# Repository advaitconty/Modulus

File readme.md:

# Modulus

A keyboard, built with the idea of expansion in the future, through SPI.

Things I will do later in the future (with other Hack Club events, or with my own money):
- Numpad over SPI
- Macropad over SPI

Just use it like a keyboard! However, any SPI accessories should be connected while the keyboard is powered down. This is mainly a limitation of SPI, as it is not hot-plug compatible.
The USB ports are USB 2.0 only, so it's better to be used for stuff like USB sound cards and mice.
I don't actually know how much lag will the ports create, because they're bottom mounted, in direct contact with foam, and is air cooled. So it may overheat (tried to add thermal dissiptation vias but effectiveness not tested)

Quirks:
- Case has holes at the bottom for cooling (yes I'm serious)

## Images

- model + board

- board only

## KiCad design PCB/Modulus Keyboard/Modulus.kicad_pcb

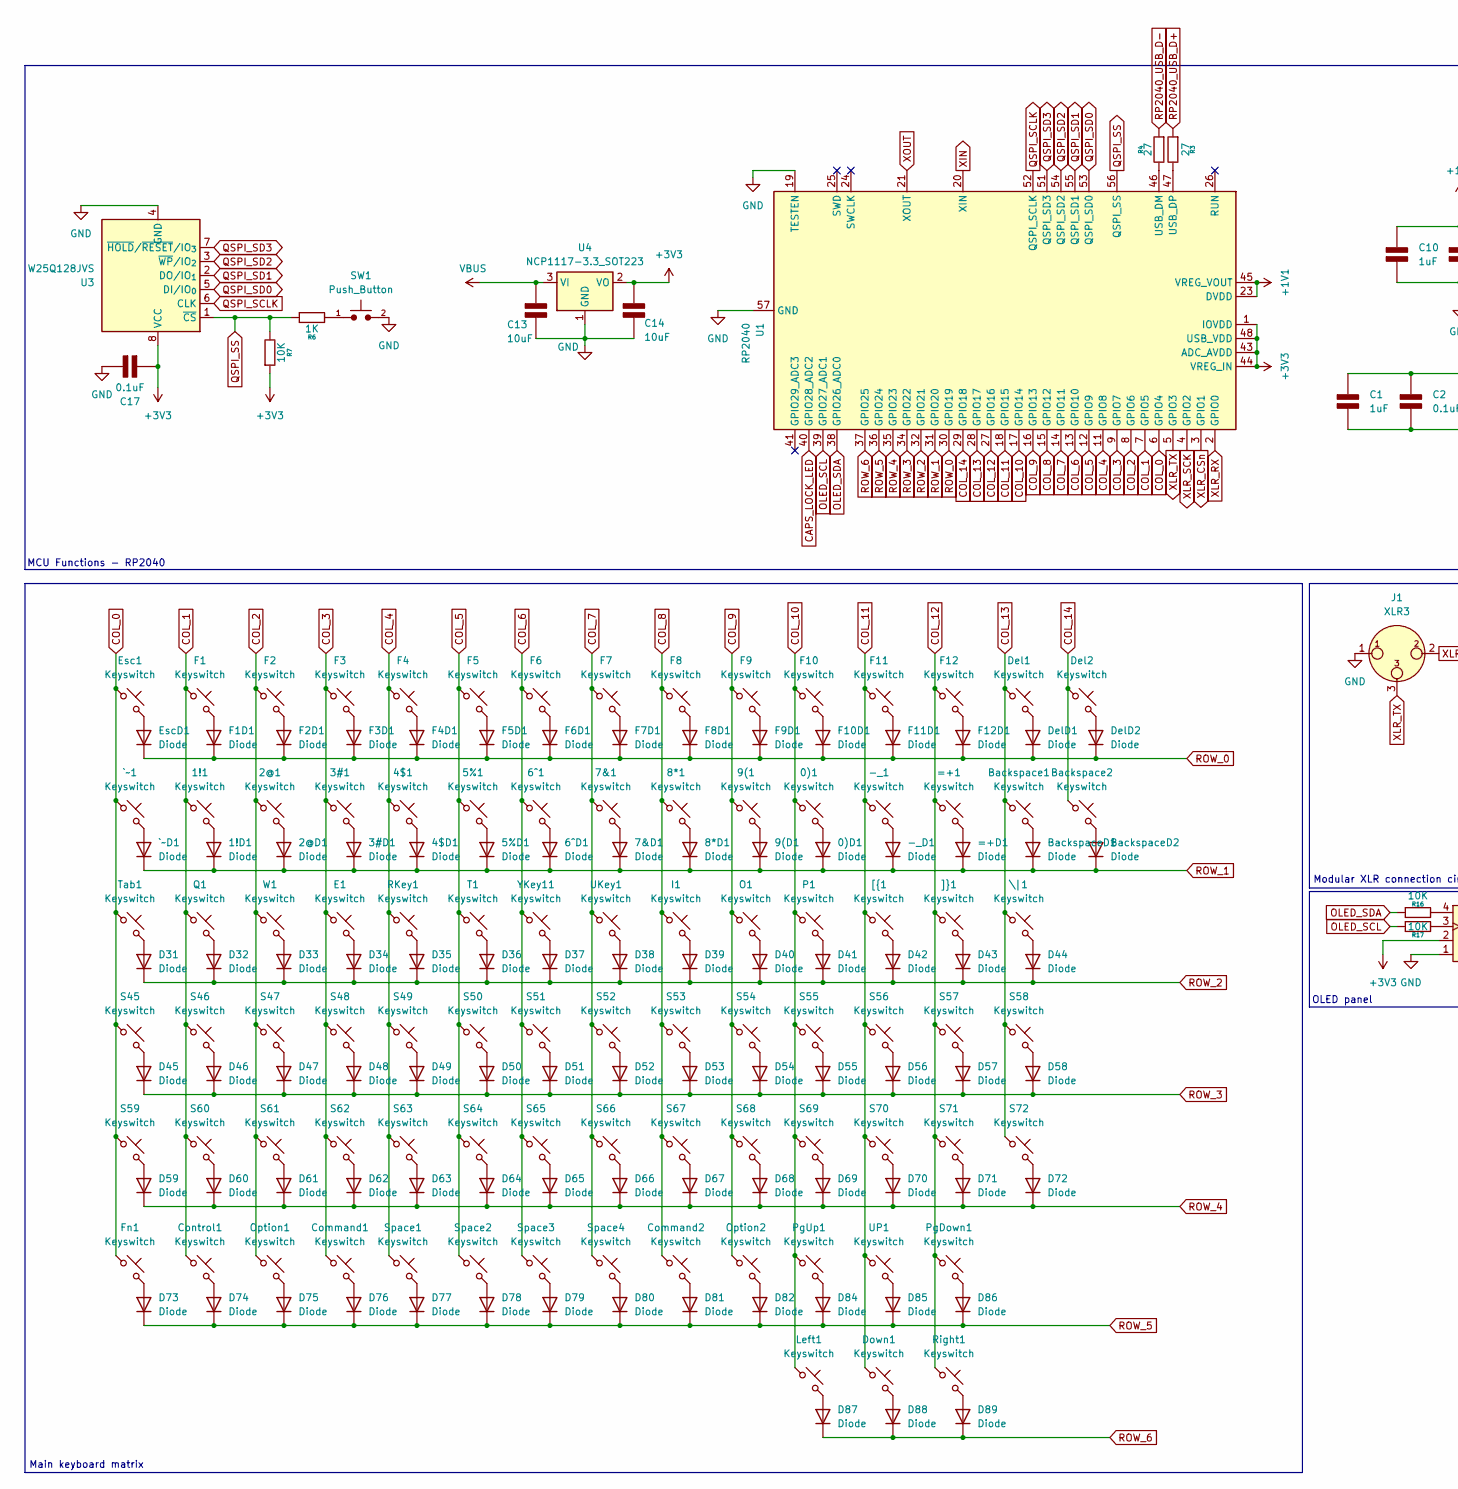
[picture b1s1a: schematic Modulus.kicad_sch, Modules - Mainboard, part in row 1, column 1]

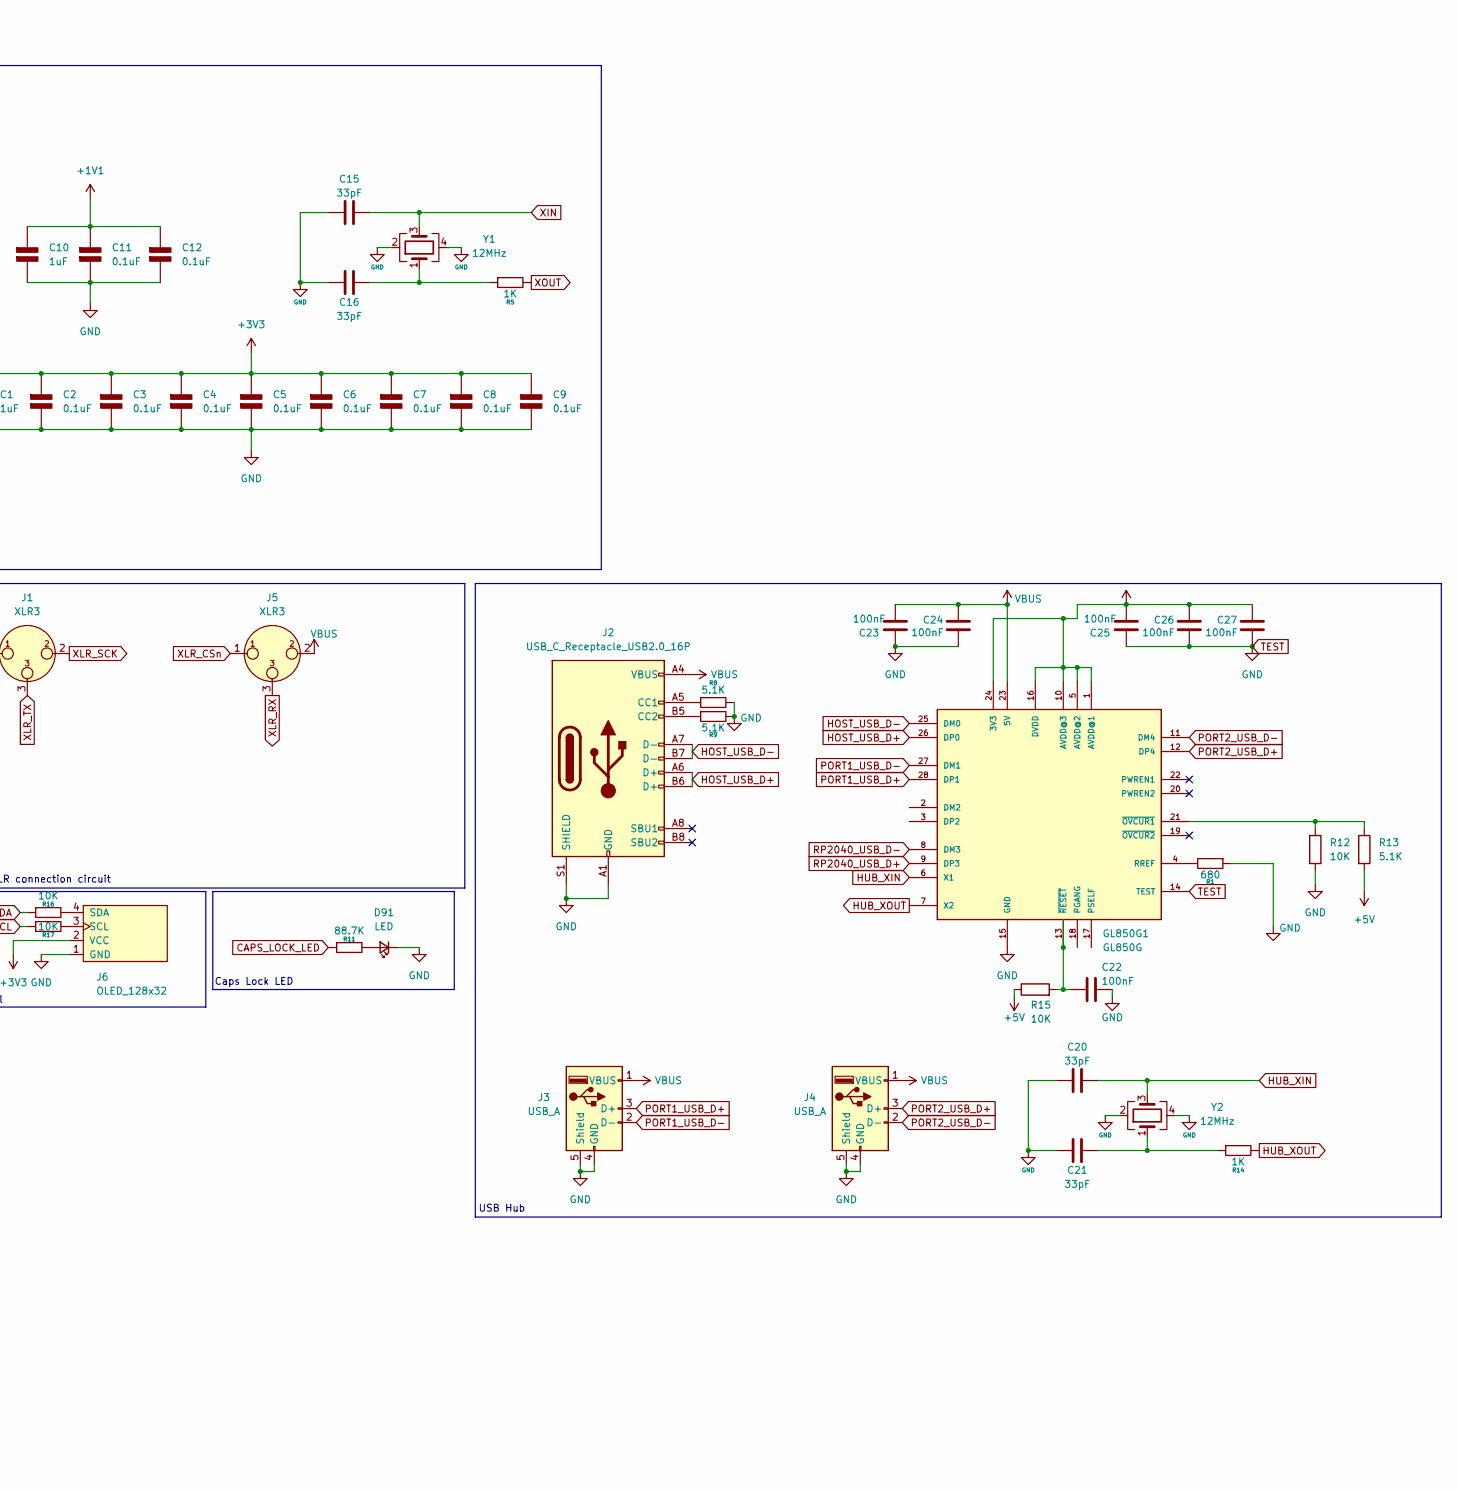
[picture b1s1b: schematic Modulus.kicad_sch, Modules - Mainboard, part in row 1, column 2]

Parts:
0)1, 1!1, 2@1, 3#1, 4$1, 5%1, 6^1, 7&1, 8*1, 9(1: Keyswitch; SW_Hotswap_Kailh_MX_1.00u; JLCPCB Part # C41430893
0)D1, 1!D1, 2@D1, 3#D1, 4$D1, 5%D1, 6^D1, 7&D1, 8*D1, 9(D1: Diode; D_SMA; JLCPCB Part # C81598
-_1: Keyswitch; SW_Hotswap_Kailh_MX_1.00u; JLCPCB Part # C41430893
-_D1: Diode; D_SMA; JLCPCB Part # C81598
=+1: Keyswitch; SW_Hotswap_Kailh_MX_1.00u; JLCPCB Part # C41430893
=+D1: Diode; D_SMA; JLCPCB Part # C81598
Backspace1, Backspace2: Keyswitch; SW_Hotswap_Kailh_MX_1.00u; JLCPCB Part # C41430893
BackspaceD1, BackspaceD2: Diode; D_SMA; JLCPCB Part # C81598
C1, C10: 1uF; C_1206_3216Metric; Rating V; JLCPCB Part # C1848
C2, C3, C4, C5, C6, C7, C8, C9, C11, C12, C17: 0.1uF; C_1206_3216Metric; Rating V; JLCPCB Part # C24497
C13, C14: 10uF; C_1206_3216Metric; Rating V; JLCPCB Part # C13585
C15, C16, C20, C21: 33pF; C_0805_2012Metric; JLCPCB Part # C107115
C22, C23, C24, C25, C26, C27: 100nF; C_1206_3216Metric; JLCPCB Part # C1848
Command1, Command2: Keyswitch; SW_Hotswap_Kailh_MX_1.00u; JLCPCB Part # C41430893
Control1: Keyswitch; SW_Hotswap_Kailh_MX_1.00u; JLCPCB Part # C41430893
D31, D32, D33, D34, D35, D36, D37, D38, D39, D40, D41, D42, D43, D44, D45, D46, D47, D48, D49, D50, D51, D52, D53, D54, D55, D56, D57, D58, D59, D60, D61, D62, D63, D64, D65, D66, D67, D68, D69, D70, D71, D72, D73, D74, D75, D76, D77, D78, D79, D80, D81, D82, D84, D85, D86, D87, D88, D89: Diode; D_SMA; JLCPCB Part # C81598
D91: LED; LED_D5.0mm
Del1, Del2: Keyswitch; SW_Hotswap_Kailh_MX_1.00u; JLCPCB Part # C41430893
DelD1, DelD2: Diode; D_SMA; JLCPCB Part # C81598
Down1: Keyswitch; SW_Hotswap_Kailh_MX_1.00u; JLCPCB Part # C41430893
E1: Keyswitch; SW_Hotswap_Kailh_MX_1.00u; JLCPCB Part # C41430893
Esc1: Keyswitch; SW_Hotswap_Kailh_MX_1.00u; JLCPCB Part # C41430893
EscD1: Diode; D_SMA; JLCPCB Part # C81598
F1, F2, F3, F4, F5, F6, F7, F8, F9, F10, F11, F12: Keyswitch; SW_Hotswap_Kailh_MX_1.00u; JLCPCB Part # C41430893
F1D1, F2D1, F3D1, F4D1, F5D1, F6D1, F7D1, F8D1, F9D1, F10D1, F11D1, F12D1: Diode; D_SMA; JLCPCB Part # C81598
Fn1: Keyswitch; SW_Hotswap_Kailh_MX_1.00u; JLCPCB Part # C41430893
GL850G1: GL850G; 28SSOP; JLCPCB Part # C7501406
I1: Keyswitch; SW_Hotswap_Kailh_MX_1.00u; JLCPCB Part # C41430893
J1, J5: XLR3; NEUTRIK_NC3FAAH; JLCPCB Part # C368521
J2: USB_C_Receptacle_USB2.0_16P; USB_C_HRO_TYPE-C-31-M-12; JLCPCB Part # C165948
J3, J4: USB_A; GCT_USB1046-GF-0190-L-B-A_REVB4; JLCPCB Part # C6307429
J6: OLED_128x32
Left1: Keyswitch; SW_Hotswap_Kailh_MX_1.00u; JLCPCB Part # C41430893
O1: Keyswitch; SW_Hotswap_Kailh_MX_1.00u; JLCPCB Part # C41430893
Option1, Option2: Keyswitch; SW_Hotswap_Kailh_MX_1.00u; JLCPCB Part # C41430893
P1: Keyswitch; SW_Hotswap_Kailh_MX_1.00u; JLCPCB Part # C41430893
PgDown1: Keyswitch; SW_Hotswap_Kailh_MX_1.00u; JLCPCB Part # C41430893
PgUp1: Keyswitch; SW_Hotswap_Kailh_MX_1.00u; JLCPCB Part # C41430893
Q1: Keyswitch; SW_Hotswap_Kailh_MX_1.00u; JLCPCB Part # C41430893
R1: 680; R_0805_2012Metric; JLCPCB Part # C17798
R3, R4: 27; R_0805_2012Metric; JLCPCB Part # C17594
R5, R6, R14: 1K; R_1206_3216Metric; JLCPCB Part # C4410
R7, R12, R15, R16, R17: 10K; R_1206_3216Metric; JLCPCB Part # C17902
R8, R9, R13: 5.1K; R_0805_2012Metric; JLCPCB Part # C27834
R11: 88.7K; R_0402_1005Metric; JLCPCB Part # C25922
RKey1: Keyswitch; SW_Hotswap_Kailh_MX_1.00u; JLCPCB Part # C41430893
Right1: Keyswitch; SW_Hotswap_Kailh_MX_1.00u; JLCPCB Part # C41430893
S45: Keyswitch; SW_Hotswap_Kailh_MX_1.75u; JLCPCB Part # C41430893
S46, S47, S48, S49, S50, S51, S52, S53, S54, S55, S56, S57, S61, S62, S63, S64, S65, S66, S67, S68, S69, S70, S71: Keyswitch; SW_Hotswap_Kailh_MX_1.00u; JLCPCB Part # C41430893
S58, S59, S60: Keyswitch; SW_Hotswap_Kailh_MX_1.25u; JLCPCB Part # C41430893
S72: Keyswitch; SW_Hotswap_Kailh_MX_1.50u; JLCPCB Part # C41430893
SW1: Push_Button; SW_PUSH_6mm
Space1, Space2, Space3, Space4: Keyswitch; SW_Hotswap_Kailh_MX_1.50u; JLCPCB Part # C41430893
T1: Keyswitch; SW_Hotswap_Kailh_MX_1.00u; JLCPCB Part # C41430893
Tab1: Keyswitch; SW_Hotswap_Kailh_MX_1.50u; JLCPCB Part # C41430893
U1: RP2040; QFN-56-1EP_7x7mm_P0.4mm_EP3.2x3.2mm; JLCPCB Part # C2040
U3: W25Q128JVS; SOIC-8_5.3x5.3mm_P1.27mm; JLCPCB Part # C97521
U4: NCP1117-3.3_SOT223; SOT-223-3_TabPin2; JLCPCB Part # C26537
UKey1: Keyswitch; SW_Hotswap_Kailh_MX_1.00u; JLCPCB Part # C41430893
UP1: Keyswitch; SW_Hotswap_Kailh_MX_1.00u; JLCPCB Part # C41430893
W1: Keyswitch; SW_Hotswap_Kailh_MX_1.00u; JLCPCB Part # C41430893
Y1, Y2: 12MHz; Crystal_SMD_3225-4Pin_3.2x2.5mm; JLCPCB Part # C9002
YKey11: Keyswitch; SW_Hotswap_Kailh_MX_1.00u; JLCPCB Part # C41430893
[{1: Keyswitch; SW_Hotswap_Kailh_MX_1.00u; JLCPCB Part # C41430893
\|1: Keyswitch; SW_Hotswap_Kailh_MX_1.50u; JLCPCB Part # C41430893
]}1: Keyswitch; SW_Hotswap_Kailh_MX_1.00u; JLCPCB Part # C41430893
`~1: Keyswitch; SW_Hotswap_Kailh_MX_1.00u; JLCPCB Part # C41430893
`~D1: Diode; D_SMA; JLCPCB Part # C81598

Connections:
+1V1: C10.1 (+), C11.1 (+), C12.1 (+), U1.23 (DVDD), U1.45 (VREG_VOUT), U1.50 (DVDD)
+3V3: C1.1 (+), C2.1 (+), C3.1 (+), C4.1 (+), C5.1 (+), C6.1 (+), C7.1 (+), C8.1 (+), C9.1 (+), C14.1 (+), C17.1 (+), C25.2, C26.2, C27.2, GL850G1.1 (AVDD@1), GL850G1.5 (AVDD@2), GL850G1.10 (AVDD@3), GL850G1.16 (DVDD), GL850G1.24 (3V3), J6.2 (VCC), R7.1, U1.1 (IOVDD), U1.10 (IOVDD), U1.22 (IOVDD), U1.33 (IOVDD), U1.42 (IOVDD), U1.43 (ADC_AVDD), U1.44 (VREG_IN), U1.48 (USB_VDD), U1.49 (IOVDD), U3.8 (VCC), U4.2 (VO)
+5V: R13.2, R15.1
CAPS_LOCK_LED: R11.1, U1.40 (GPIO28_ADC2)
COL_0: Esc1.1, Fn1.1, S45.1, S59.1, Tab1.1, U1.6 (GPIO4), `~1.1
COL_1: 1!1.1, Control1.1, F1.1, Q1.1, S46.1, S60.1, U1.7 (GPIO5)
COL_2: 2@1.1, F2.1, Option1.1, S47.1, S61.1, U1.8 (GPIO6), W1.1
COL_3: 3#1.1, Command1.1, E1.1, F3.1, S48.1, S62.1, U1.9 (GPIO7)
COL_4: 4$1.1, F4.1, RKey1.1, S49.1, S63.1, Space1.1, U1.11 (GPIO8)
COL_5: 5%1.1, F5.1, S50.1, S64.1, Space2.1, T1.1, U1.12 (GPIO9)
COL_6: 6^1.1, F6.1, S51.1, S65.1, Space3.1, U1.13 (GPIO10), YKey11.1
COL_7: 7&1.1, F7.1, S52.1, S66.1, Space4.1, U1.14 (GPIO11), UKey1.1
COL_8: 8*1.1, Command2.1, F8.1, I1.1, S53.1, S67.1, U1.15 (GPIO12)
COL_9: 9(1.1, F9.1, O1.1, Option2.1, S54.1, S68.1, U1.16 (GPIO13)
COL_10: 0)1.1, F10.1, Left1.1, P1.1, PgUp1.1, S55.1, S69.1, U1.17 (GPIO14)
COL_11: -_1.1, Down1.1, F11.1, S56.1, S70.1, U1.18 (GPIO15), UP1.1, [{1.1
COL_12: =+1.1, F12.1, PgDown1.1, Right1.1, S57.1, S71.1, U1.27 (GPIO16), ]}1.1
COL_13: Backspace1.1, Del1.1, S58.1, S72.1, U1.28 (GPIO17), \|1.1
COL_14: Backspace2.1, Del2.1, U1.29 (GPIO18)
HOST_USB_D+: GL850G1.26 (DP0), J2.A6 (D+), J2.B6 (D+)
HOST_USB_D-: GL850G1.25 (DM0), J2.A7 (D-), J2.B7 (D-)
HUB_XIN: C20.2, GL850G1.6 (X1), Y2.3
HUB_XOUT: GL850G1.7 (X2), R14.2
unnamed: 0)1.2, 0)D1.2 (A)
unnamed: 1!1.2, 1!D1.2 (A)
unnamed: 2@1.2, 2@D1.2 (A)
unnamed: 3#1.2, 3#D1.2 (A)
unnamed: 4$1.2, 4$D1.2 (A)
unnamed: 5%1.2, 5%D1.2 (A)
unnamed: 6^1.2, 6^D1.2 (A)
unnamed: 7&1.2, 7&D1.2 (A)
unnamed: 8*1.2, 8*D1.2 (A)
unnamed: 9(1.2, 9(D1.2 (A)
unnamed: -_1.2, -_D1.2 (A)
unnamed: =+1.2, =+D1.2 (A)
unnamed: Backspace1.2, BackspaceD1.2 (A)
unnamed: Backspace2.2, BackspaceD2.2 (A)
unnamed: C16.2, R5.1, Y1.1
unnamed: C21.2, R14.1, Y2.1
unnamed: D31.2 (A), Tab1.2
unnamed: D32.2 (A), Q1.2
unnamed: D33.2 (A), W1.2
unnamed: D34.2 (A), E1.2
unnamed: D35.2 (A), RKey1.2
unnamed: D36.2 (A), T1.2
unnamed: D37.2 (A), YKey11.2
unnamed: D38.2 (A), UKey1.2
unnamed: D39.2 (A), I1.2
unnamed: D40.2 (A), O1.2
unnamed: D41.2 (A), P1.2
unnamed: D42.2 (A), [{1.2
unnamed: D43.2 (A), ]}1.2
unnamed: D44.2 (A), \|1.2
unnamed: D45.2 (A), S45.2
unnamed: D46.2 (A), S46.2
unnamed: D47.2 (A), S47.2
unnamed: D48.2 (A), S48.2
unnamed: D49.2 (A), S49.2
unnamed: D50.2 (A), S50.2
unnamed: D51.2 (A), S51.2
unnamed: D52.2 (A), S52.2
unnamed: D53.2 (A), S53.2
unnamed: D54.2 (A), S54.2
unnamed: D55.2 (A), S55.2
unnamed: D56.2 (A), S56.2
unnamed: D57.2 (A), S57.2
unnamed: D58.2 (A), S58.2
unnamed: D59.2 (A), S59.2
unnamed: D60.2 (A), S60.2
unnamed: D61.2 (A), S61.2
unnamed: D62.2 (A), S62.2
unnamed: D63.2 (A), S63.2
unnamed: D64.2 (A), S64.2
unnamed: D65.2 (A), S65.2
unnamed: D66.2 (A), S66.2
unnamed: D67.2 (A), S67.2
unnamed: D68.2 (A), S68.2
unnamed: D69.2 (A), S69.2
unnamed: D70.2 (A), S70.2
unnamed: D71.2 (A), S71.2
unnamed: D72.2 (A), S72.2
unnamed: D73.2 (A), Fn1.2
unnamed: Control1.2, D74.2 (A)
unnamed: D75.2 (A), Option1.2
unnamed: Command1.2, D76.2 (A)
unnamed: D77.2 (A), Space1.2
unnamed: D78.2 (A), Space2.2
unnamed: D79.2 (A), Space3.2
unnamed: D80.2 (A), Space4.2
unnamed: Command2.2, D81.2 (A)
unnamed: D82.2 (A), Option2.2
unnamed: D84.2 (A), PgUp1.2
unnamed: D85.2 (A), UP1.2
unnamed: D86.2 (A), PgDown1.2
unnamed: D87.2 (A), Left1.2
unnamed: D88.2 (A), Down1.2
unnamed: D89.2 (A), Right1.2
unnamed: D91.2 (A), R11.2
unnamed: Del1.2, DelD1.2 (A)
unnamed: Del2.2, DelD2.2 (A)
unnamed: Esc1.2, EscD1.2 (A)
unnamed: F1.2, F1D1.2 (A)
unnamed: F2.2, F2D1.2 (A)
unnamed: F3.2, F3D1.2 (A)
unnamed: F4.2, F4D1.2 (A)
unnamed: F5.2, F5D1.2 (A)
unnamed: F6.2, F6D1.2 (A)
unnamed: F7.2, F7D1.2 (A)
unnamed: F8.2, F8D1.2 (A)
unnamed: F9.2, F9D1.2 (A)
unnamed: F10.2, F10D1.2 (A)
unnamed: F11.2, F11D1.2 (A)
unnamed: F12.2, F12D1.2 (A)
unnamed: GL850G1.4 (RREF), R1.2
unnamed: GL850G1.21 (~OVCUR1), R12.1, R13.1
unnamed: C22.2, GL850G1.13 (~RESET), R15.2
unnamed: J2.A5 (CC1), R8.1
unnamed: J2.B5 (CC2), R9.1
unnamed: J6.3 (SCL), R17.2
unnamed: J6.4 (SDA), R16.2
unnamed: R6.2, SW1.1
unnamed: R4.2, U1.46 (USB_DM)
unnamed: R3.2, U1.47 (USB_DP)
unnamed: `~1.2, `~D1.2 (A)
OLED_SCL: R17.1, U1.39 (GPIO27_ADC1)
OLED_SDA: R16.1, U1.38 (GPIO26_ADC0)
PORT1_USB_D+: GL850G1.28 (DP1), J3.3 (D+)
PORT1_USB_D-: GL850G1.27 (DM1), J3.2 (D-)
PORT2_USB_D+: GL850G1.12 (DP4), J4.3 (D+)
PORT2_USB_D-: GL850G1.11 (DM4), J4.2 (D-)
QSPI_SCLK: U1.52 (QSPI_SCLK), U3.6 (CLK)
QSPI_SD0: U1.53 (QSPI_SD0), U3.5 (DI/IO_{0})
QSPI_SD1: U1.55 (QSPI_SD1), U3.2 (DO/IO_{1})
QSPI_SD2: U1.54 (QSPI_SD2), U3.3 (~WP/IO_{2})
QSPI_SD3: U1.51 (QSPI_SD3), U3.7 (~HOLD/~RESET/IO_{3})
QSPI_SS: R6.1, R7.2, U1.56 (QSPI_SS), U3.1 (~CS)
ROW_0: DelD1.1 (K), DelD2.1 (K), EscD1.1 (K), F1D1.1 (K), F2D1.1 (K), F3D1.1 (K), F4D1.1 (K), F5D1.1 (K), F6D1.1 (K), F7D1.1 (K), F8D1.1 (K), F9D1.1 (K), F10D1.1 (K), F11D1.1 (K), F12D1.1 (K), U1.30 (GPIO19)
ROW_1: 0)D1.1 (K), 1!D1.1 (K), 2@D1.1 (K), 3#D1.1 (K), 4$D1.1 (K), 5%D1.1 (K), 6^D1.1 (K), 7&D1.1 (K), 8*D1.1 (K), 9(D1.1 (K), -_D1.1 (K), =+D1.1 (K), BackspaceD1.1 (K), BackspaceD2.1 (K), U1.31 (GPIO20), `~D1.1 (K)
ROW_2: D31.1 (K), D32.1 (K), D33.1 (K), D34.1 (K), D35.1 (K), D36.1 (K), D37.1 (K), D38.1 (K), D39.1 (K), D40.1 (K), D41.1 (K), D42.1 (K), D43.1 (K), D44.1 (K), U1.32 (GPIO21)
ROW_3: D45.1 (K), D46.1 (K), D47.1 (K), D48.1 (K), D49.1 (K), D50.1 (K), D51.1 (K), D52.1 (K), D53.1 (K), D54.1 (K), D55.1 (K), D56.1 (K), D57.1 (K), D58.1 (K), U1.34 (GPIO22)
ROW_4: D59.1 (K), D60.1 (K), D61.1 (K), D62.1 (K), D63.1 (K), D64.1 (K), D65.1 (K), D66.1 (K), D67.1 (K), D68.1 (K), D69.1 (K), D70.1 (K), D71.1 (K), D72.1 (K), U1.35 (GPIO23)
ROW_5: D73.1 (K), D74.1 (K), D75.1 (K), D76.1 (K), D77.1 (K), D78.1 (K), D79.1 (K), D80.1 (K), D81.1 (K), D82.1 (K), D84.1 (K), D85.1 (K), D86.1 (K), U1.36 (GPIO24)
ROW_6: D87.1 (K), D88.1 (K), D89.1 (K), U1.37 (GPIO25)
RP2040_USB_D+: GL850G1.9 (DP3), R3.1
RP2040_USB_D-: GL850G1.8 (DM3), R4.1
TEST: C1.2 (-), C2.2 (-), C3.2 (-), C4.2 (-), C5.2 (-), C6.2 (-), C7.2 (-), C8.2 (-), C9.2 (-), C10.2 (-), C11.2 (-), C12.2 (-), C13.2 (-), C14.2 (-), C15.1, C16.1, C17.2 (-), C20.1, C21.1, C22.1, C23.1, C24.1, C25.1, C26.1, C27.1, D91.1 (K), GL850G1.14 (TEST), GL850G1.15 (GND), J1.1, J2.A1 (GND), J2.A12 (GND), J2.B1 (GND), J2.B12 (GND), J2.S1 (SHIELD), J3.4 (GND), J3.5 (Shield), J4.4 (GND), J4.5 (Shield), J6.1 (GND), R1.1, R8.2, R9.2, R12.2, SW1.2, U1.19 (TESTEN), U1.57 (GND), U3.4 (GND), U4.1 (GND), Y1.2, Y1.4, Y2.2, Y2.4
VBUS: C13.1 (+), C23.2, C24.2, GL850G1.23 (5V), J2.A4 (VBUS), J2.A9 (VBUS), J2.B4 (VBUS), J2.B9 (VBUS), J3.1 (VBUS), J4.1 (VBUS), J5.2, U4.3 (VI)
XIN: C15.2, U1.20 (XIN), Y1.3
XLR_CSn: J5.1, U1.3 (GPIO1)
XLR_RX: J5.3, U1.2 (GPIO0)
XLR_SCK: J1.2, U1.4 (GPIO2)
XLR_TX: J1.3, U1.5 (GPIO3)
XOUT: R5.2, U1.21 (XOUT)

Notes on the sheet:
Caps Lock LED
OLED panel
USB Hub
Modular XLR connection circuit
MCU Functions - RP2040
Main keyboard matrix

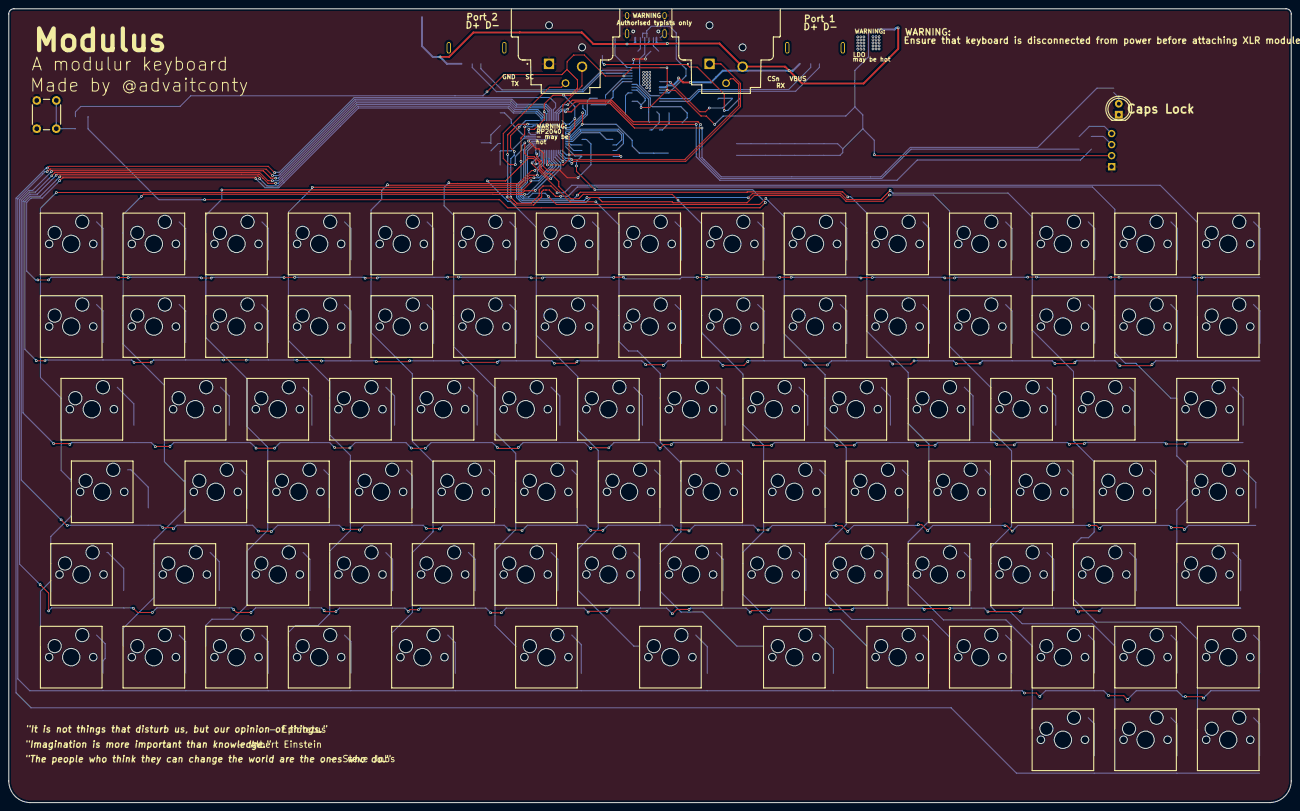
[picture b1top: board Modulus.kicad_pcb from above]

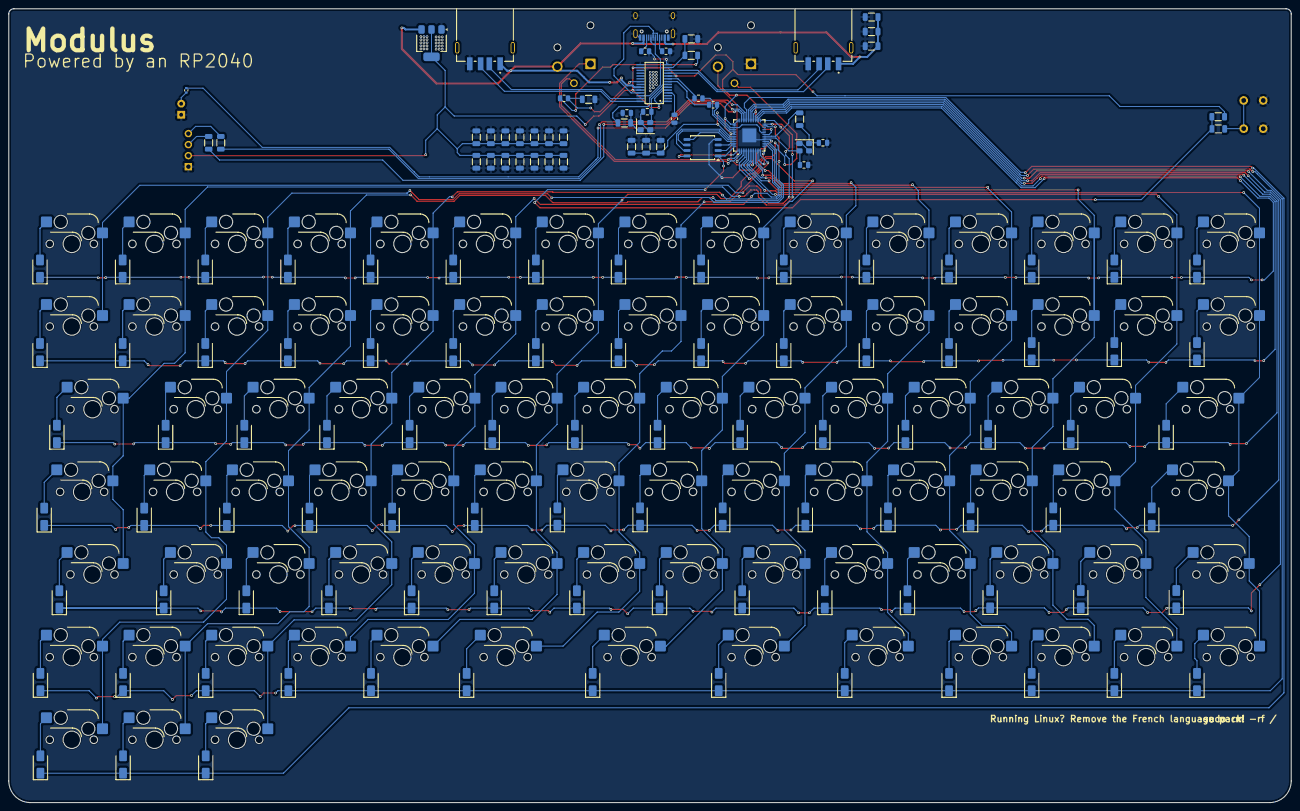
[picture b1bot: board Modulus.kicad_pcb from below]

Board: 2 copper layers, 295.6 x 183.0 mm, 230 parts (137 on the bottom side), 153 nets.

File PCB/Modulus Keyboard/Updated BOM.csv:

"Id";"Designator";"Footprint";"Quantity";"Designation";"Supplier and ref";
1;"U4";"SOT-223-3_TabPin2";1;"NCP1117-3.3_SOT223";;;
2;"Caps Lock";"0603";1;"LED";;;
3;"R6,R14,R5";"R_1206_3216Metric";3;"1K";;;
4;"R4,R3";"R_0805_2012Metric";2;"27";;;
5;"C9,C7,C12,C17,C6,C11,C3,C4,C2,C5,C8";"C_1206_3216Metric";11;"0.1uF";;;
6;"S47,F9,Command1,S51,S55,YKey11,PgUp1,S65,P1,S69,9(1,5%1,1!1,S56,Q1,0)1,F12,-_1,Backspace2,RKey1,S53,Command2,T1,S71,4$1,S68,S52,S54,F10,S63,Option1,]}1,S67,F8,S61,S50,Left1,S66,`~1,S62,S49,Backspace1,E1,F3,F11,Del1,I1,Control1,7&1,F2,Option2,8*1,Down1,2@1,F6,S48,F1,[{1,S70,UP1,Fn1,F5,Esc1,W1,O1,3#1,S64,6^1,Right1,Del2,PgDown1,F4,S46,F7,=+1,UKey1,S57";"Hotswap_MX_1.00u";77;"Keyswitch";;;
7;"S58,S59,S60";"Hotswap_MX_1.25u";3;"Keyswitch";;;
8;"GL850G1";"28SSOP";1;"GL850G";;;
9;"R1";"R_0805_2012Metric";1;"680";;;
10;"Y2,Y1";"Crystal_SMD_3225-4Pin_3.2x2.5mm";2;"12MHz";;;
11;"C21,C16,C20,C15";"C_0805_2012Metric";4;"33pF";;;
12;"R11";"R_0402_1005Metric";1;"88.7K";;;
13;"C26,C27,C24,C23,C25,C22";"C_1206_3216Metric";6;"100nF";;;
14;"C1,C10";"C_1206_3216Metric";2;"1uF";;;
15;"J6";"OLED_128x32";1;"OLED_128x32";;;
16;"U1";"QFN-56-1EP_7x7mm_P0.4mm_EP3.2x3.2mm";1;"RP2040";;;
17;"U3";"SOIC-8_5.3x5.3mm_P1.27mm";1;"W25Q128JVS";;;
18;"Space1,Tab1,Space3,Space2,Space4,S72,\|1";"Hotswap_MX_1.50u";7;"Keyswitch";;;
19;"R9,R13,R8";"R_0805_2012Metric";3;"5.1K";;;
20;"R17,R16";"R_1206_3216Metric";2;"10k";;;
21;"R7,R12,R15";"R_1206_3216Metric";3;"10K";;;
22;"S45";"Hotswap_MX_1.75u";1;"Keyswitch";;;
23;"C14,C13";"C_1206_3216Metric";2;"10uF";;;
24;"J3,J4";"GCT_USB1046-GF-0190-L-B-A_REVB4";2;"USB_A";;;
25;"J1,J5";"NEUTRIK_NC3FAAH";2;"XLR3";;;
26;"J2";"USB_C_HRO_TYPE-C-31-M-12";1;"USB_C_Receptacle_USB2.0_16P";;;
27;"D62,F3D1,F11D1,F9D1,D72,D71,D56,D40,D33,9(D1,F6D1,5%D1,D61,D43,D89,DelD1,D79,D37,D70,D42,D81,D77,D39,D78,D73,F10D1,D38,D55,D57,D69,D49,-_D1,D63,D74,DelD2,EscD1,D41,D86,F2D1,F1D1,D80,D45,`~D1,F7D1,D52,8*D1,D66,D65,D82,F8D1,D34,7&D1,4$D1,D54,D68,0)D1,D50,D58,D32,D88,D36,1!D1,D51,BackspaceD1,D35,D46,D67,F5D1,D44,D48,BackspaceD2,D75,D76,D59,F4D1,D47,D87,D31,2@D1,=+D1,D64,F12D1,D53,D85,6^D1,D84,3#D1,D60";"D_SMA";88;"Diode";;;

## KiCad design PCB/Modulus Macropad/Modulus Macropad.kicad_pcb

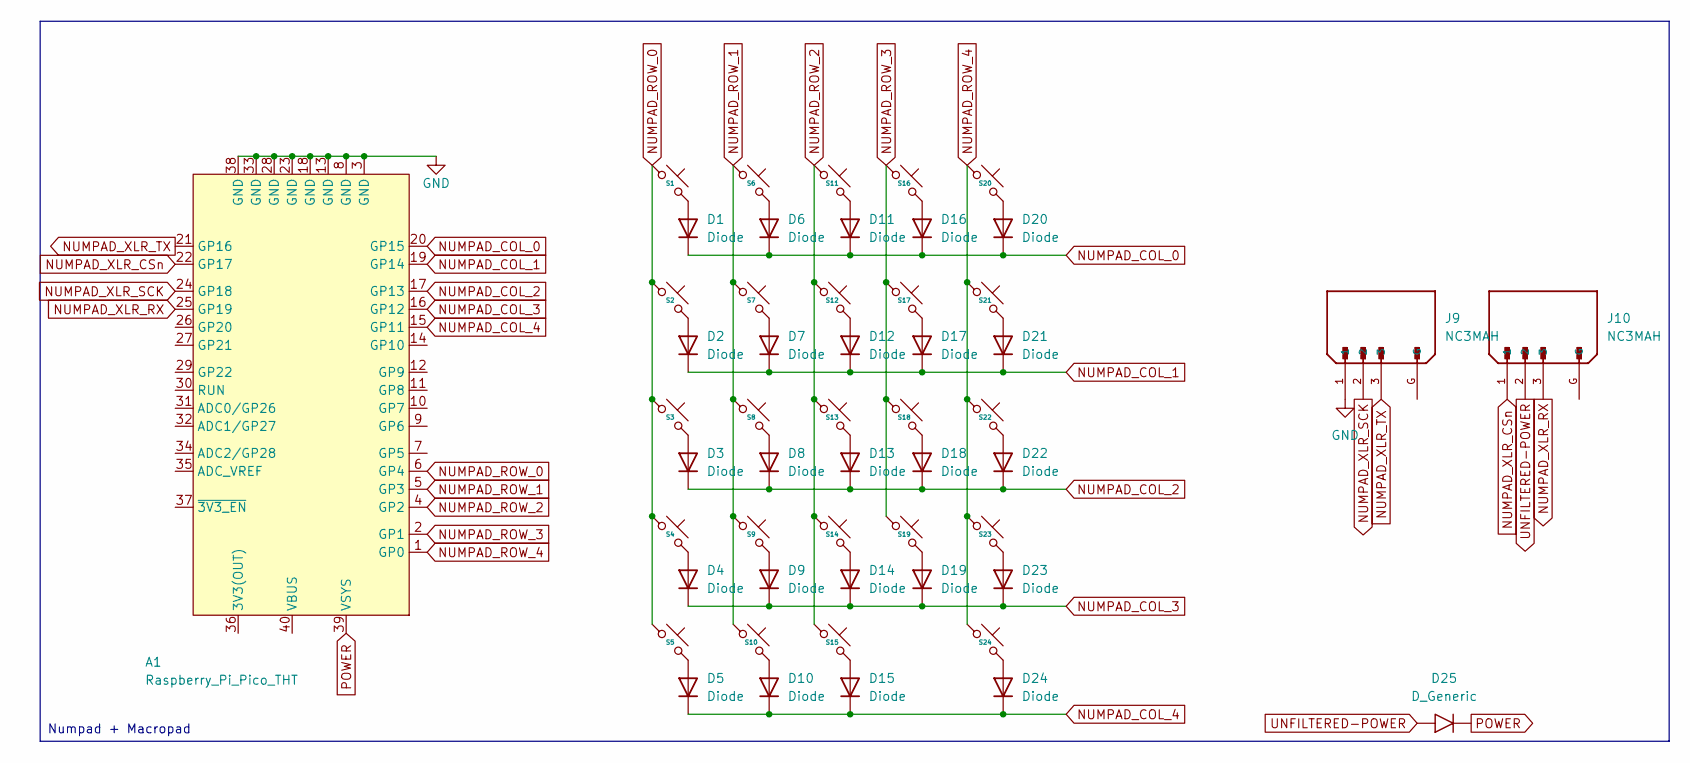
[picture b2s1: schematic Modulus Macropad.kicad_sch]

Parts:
A1: Raspberry_Pi_Pico_THT; raspberry_pi_pico_THT
D1, D2, D3, D4, D5, D6, D7, D8, D9, D10, D11, D12, D13, D14, D15, D16, D17, D18, D19, D20, D21, D22, D23, D24: Diode; D_SMA; JLCPCB Part # C81598
D25: D_Generic; D_SMA
J9, J10: NC3MAH; NEUTRIK_NC3MAH; PARTREV 30.03.09
S1, S2, S3, S4, S5, S6, S7, S8, S9, S10, S11, S12, S13, S14, S15, S16, S17, S20, S21, S22, S23, S24: SW_Hotswap_Kailh_MX_1.00u
S18, S19: SW_Hotswap_Kailh_MX_1.50u_90deg

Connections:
NUMPAD_COL_0: A1.20 (GP15), D1.1 (K), D6.1 (K), D11.1 (K), D16.1 (K), D20.1 (K)
NUMPAD_COL_1: A1.19 (GP14), D2.1 (K), D7.1 (K), D12.1 (K), D17.1 (K), D21.1 (K)
NUMPAD_COL_2: A1.17 (GP13), D3.1 (K), D8.1 (K), D13.1 (K), D18.1 (K), D22.1 (K)
NUMPAD_COL_3: A1.16 (GP12), D4.1 (K), D9.1 (K), D14.1 (K), D19.1 (K), D23.1 (K)
NUMPAD_COL_4: A1.15 (GP11), D5.1 (K), D10.1 (K), D15.1 (K), D24.1 (K)
NUMPAD_ROW_0: A1.6 (GP4), S1.1, S2.1, S3.1, S4.1, S5.1
NUMPAD_ROW_1: A1.5 (GP3), S6.1, S7.1, S8.1, S9.1, S10.1
NUMPAD_ROW_2: A1.4 (GP2), S11.1, S12.1, S13.1, S14.1, S15.1
NUMPAD_ROW_3: A1.2 (GP1), S16.1, S17.1, S18.1, S19.1
NUMPAD_ROW_4: A1.1 (GP0), S20.1, S21.1, S22.1, S23.1, S24.1
NUMPAD_XLR_CSn: A1.22 (GP17), J10.1
NUMPAD_XLR_RX: A1.25 (GP19), J10.3
NUMPAD_XLR_SCK: A1.24 (GP18), J9.2
NUMPAD_XLR_TX: A1.21 (GP16), J9.3
unnamed: D1.2 (A), S1.2
unnamed: D2.2 (A), S2.2
unnamed: D3.2 (A), S3.2
unnamed: D4.2 (A), S4.2
unnamed: D5.2 (A), S5.2
unnamed: D6.2 (A), S6.2
unnamed: D7.2 (A), S7.2
unnamed: D8.2 (A), S8.2
unnamed: D9.2 (A), S9.2
unnamed: D10.2 (A), S10.2
unnamed: D11.2 (A), S11.2
unnamed: D12.2 (A), S12.2
unnamed: D13.2 (A), S13.2
unnamed: D14.2 (A), S14.2
unnamed: D15.2 (A), S15.2
unnamed: D16.2 (A), S16.2
unnamed: D17.2 (A), S17.2
unnamed: D18.2 (A), S18.2
unnamed: D19.2 (A), S19.2
unnamed: D20.2 (A), S20.2
unnamed: D21.2 (A), S21.2
unnamed: D22.2 (A), S22.2
unnamed: D23.2 (A), S23.2
unnamed: D24.2 (A), S24.2
POWER: A1.39 (VSYS), D25.1 (K)
TEST: A1.3 (GND), A1.8 (GND), A1.13 (GND), A1.18 (GND), A1.23 (GND), A1.28 (GND), A1.33 (GND), A1.38 (GND), J9.1
UNFILTERED-POWER: D25.2 (A), J10.2

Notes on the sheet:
Numpad + Macropad

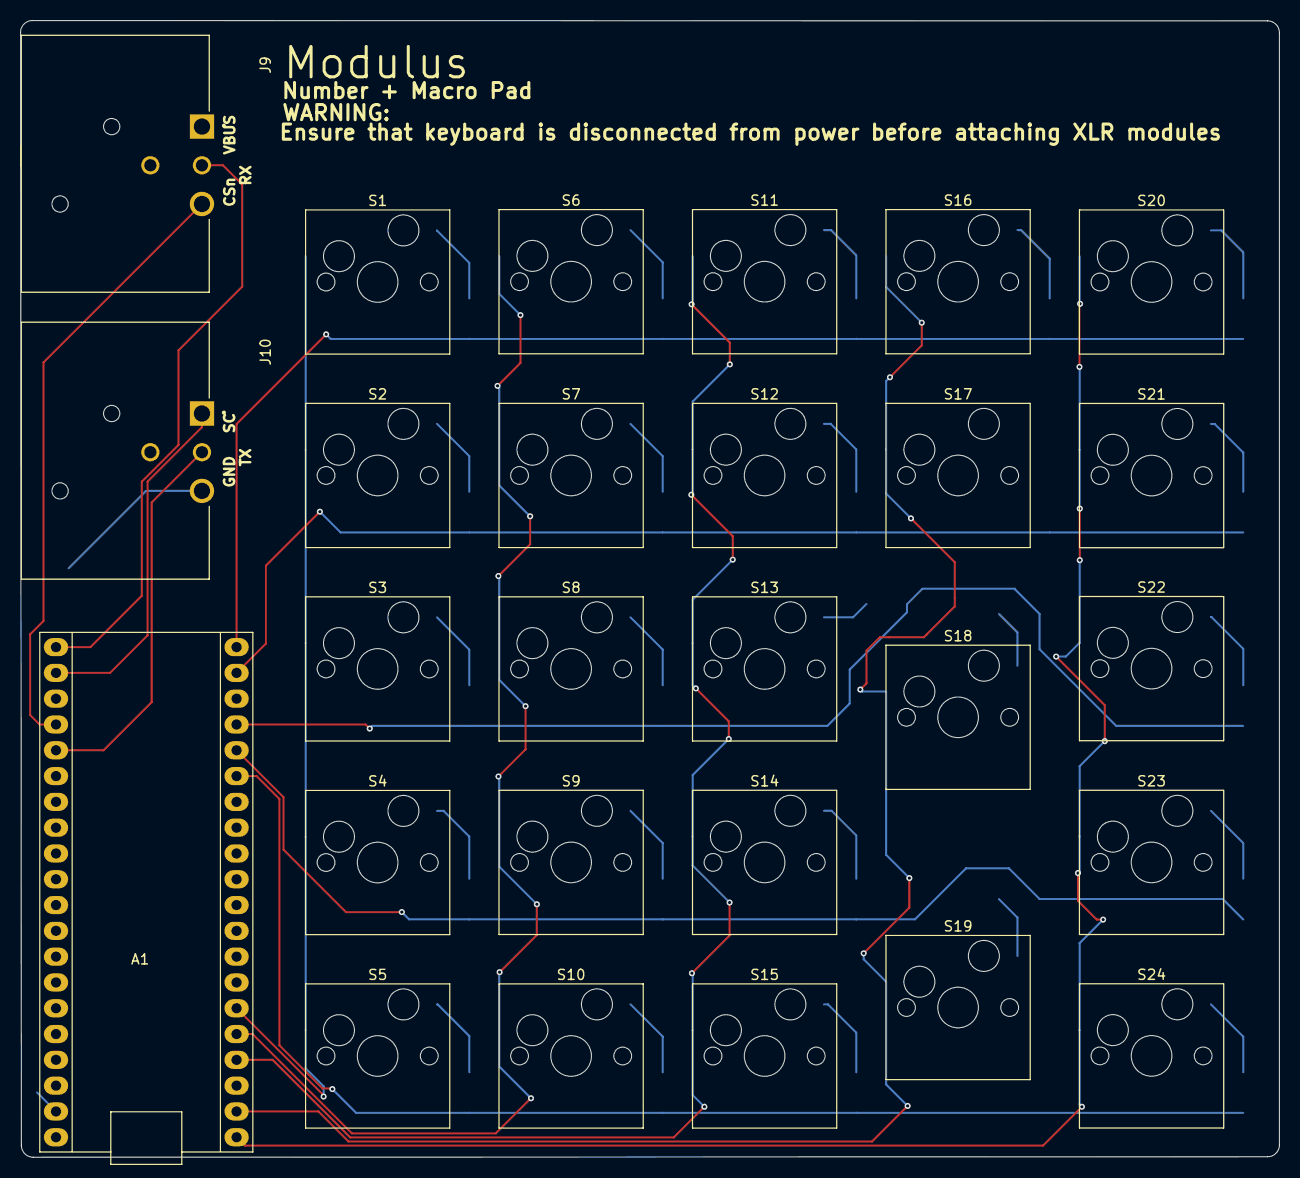
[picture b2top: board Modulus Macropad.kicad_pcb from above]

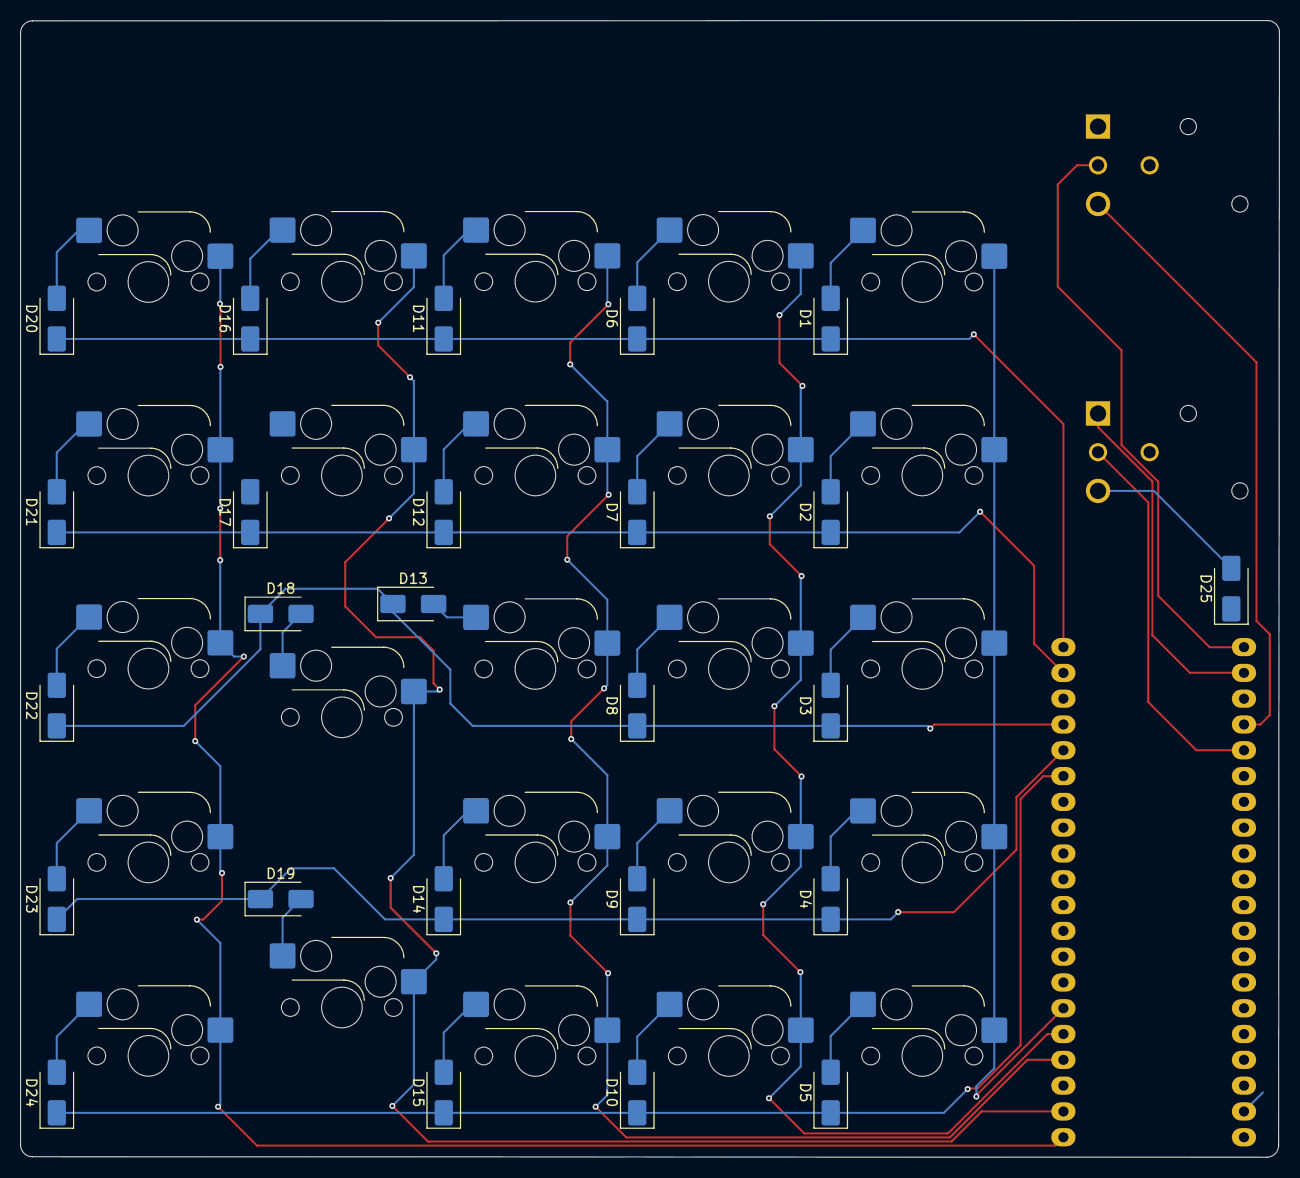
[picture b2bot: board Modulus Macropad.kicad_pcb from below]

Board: 2 copper layers, 123.9 x 111.9 mm, 52 parts (25 on the bottom side), 41 nets.

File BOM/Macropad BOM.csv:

Comment,Designator,Footprint,JLCPCB Part #
~,"S18,S1,S10,S11,S12,S13,S14,S15,S16,S17,S2,S20,S21,S22,S23,S24,S3,S4,S5,S6,S7,S8,S9,S18,S1,S10,S11,S12,S13,S14,S15,S16,S17,S2,S20,S21,S22,S23,S24,S3,S4,S5,S6,S7,S8,S9",SW_Hotswap_Kailh_MX_1.00u,C41430893
Diode,"D25,D1,D10,D11,D12,D13,D14,D15,D16,D17,D18,D19,D2,D20,D21,D22,D23,D24,D3,D4,D5,D6,D7,D8,D9,D25,D1,D10,D11,D12,D13,D14,D15,D16,D17,D18,D19,D2,D20,D21,D22,D23,D24,D3,D4,D5,D6,D7,D8,D9",D_SMA,C81598

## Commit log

2025-10-20 added LEDs, may remove
2025-10-20 added a USB hub but don't really understand shit rn
2025-10-20 added my own OLED screen, XLR ports, and a caps lock LEd
2025-10-20 Finished the schematic design for this! creating modular boardas another project
2025-10-27 ts so difficult :sob: - anyways completed wiring first row, and the MCUs
2025-10-31 wired everything, but didn't run DRC-
2026-01-27 rewired some stuff, added some new stuff
2026-03-13 rerouted AGAIn
2026-03-14 finished the case and PCB designls doing BOM now
2026-03-15 redesigning whole board so everything is at the back except the XLR stuff :pf:
2026-03-15 Moved everything to the back
2026-03-16 did clean up
2026-03-16 more clean up
2026-03-16 ready to ship!
2026-03-16 readme update
2026-03-16 added git lfs
2026-03-17 added numpad+macropad
2026-03-18 removed lock file
2026-03-18 added firmware, and new models
2026-03-18 final commit for submission
2026-03-28 Updated BOM
